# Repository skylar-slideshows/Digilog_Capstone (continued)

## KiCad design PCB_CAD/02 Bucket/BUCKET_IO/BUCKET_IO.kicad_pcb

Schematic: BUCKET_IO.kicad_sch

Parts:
J1: INPUTS; PinHeader_1x08_P2.54mm_Vertical
J2: INSERT; PinHeader_1x08_P2.54mm_Vertical
J3: IN; Jack_XLR-6.35mm_Neutrik_NCJ6FI-V-0_Vertical
J4: INSERT_OUT; Jack_6.35mm_Neutrik_NJ5FD-V_Vertical
J5: INSERT_RTN; Jack_6.35mm_Neutrik_NJ5FD-V_Vertical
J6: HI-Z; Jack_6.35mm_Neutrik_NJ5FD-V_Vertical

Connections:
/HIZ_IN: J1.7, J6.T
/INS_RTN+: J2.5, J5.T
/INS_RTN-: J2.7, J5.R
/INS_SEND+: J2.1, J4.T
/INS_SEND-: J2.3, J4.R
/LINE_COLD: J1.5, J3.R
/LINE_HOT: J1.4, J3.T
/MIC_COLD: J1.2, J3.3
/MIC_HOT: J1.1, J3.2
GND: J1.3, J1.6, J1.8, J2.2, J2.4, J2.6, J2.8, J3.1, J3.G, J3.S, J4.S, J5.S, J6.R, J6.S

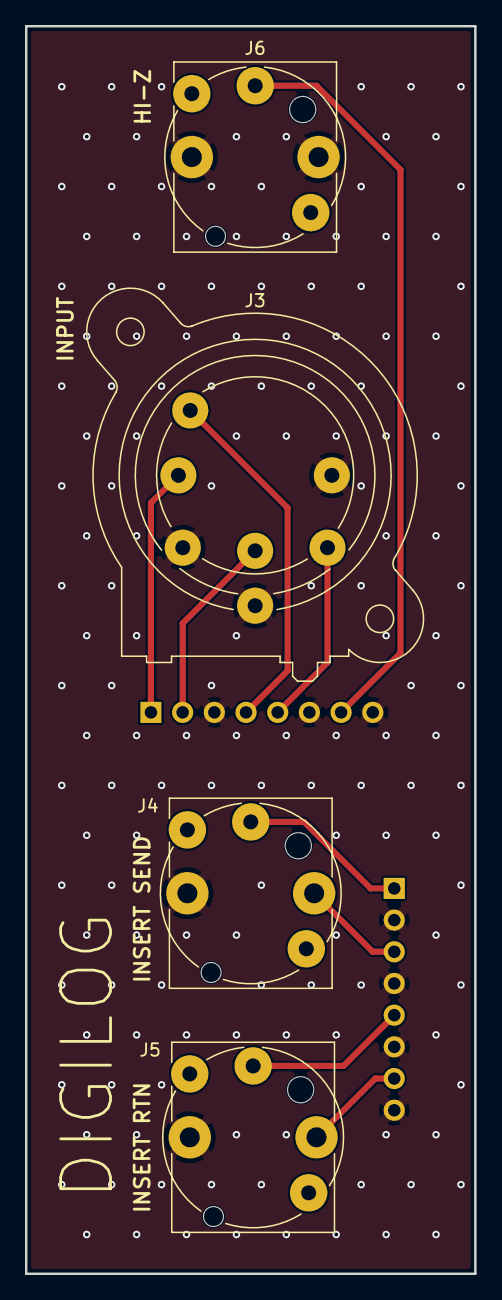
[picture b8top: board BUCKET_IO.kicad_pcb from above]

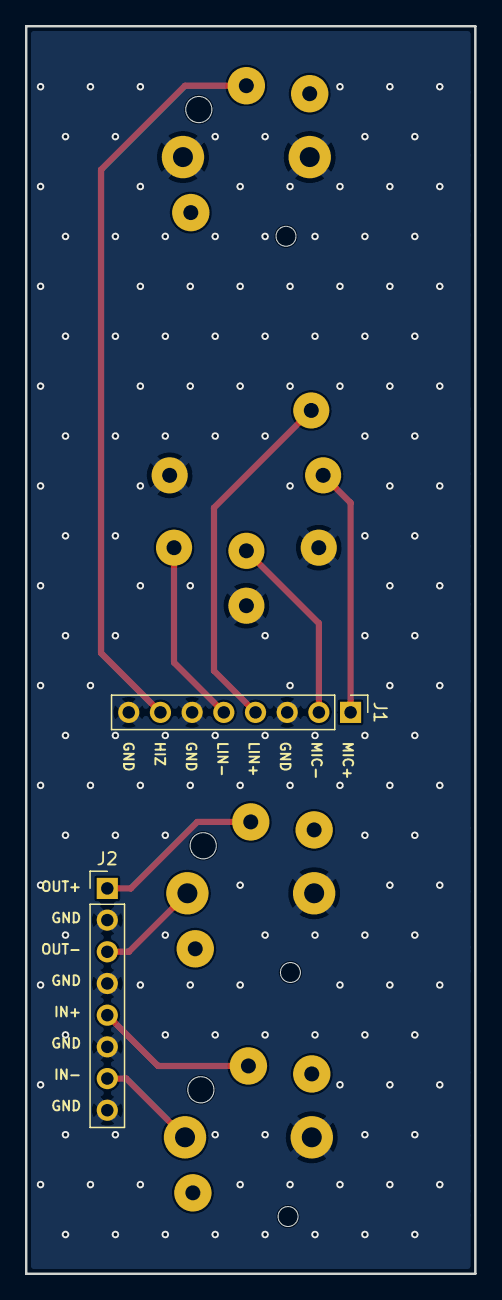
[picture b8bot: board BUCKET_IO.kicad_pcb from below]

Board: 2 copper layers, 36.0 x 100.0 mm, 6 parts (2 on the bottom side), 10 nets.

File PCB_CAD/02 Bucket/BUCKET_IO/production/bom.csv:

Designator,Footprint,Quantity,Value,LCSC Part #
J1,PinHeader_1x08_P2.54mm_Vertical,1,INPUTS,
J2,PinHeader_1x08_P2.54mm_Vertical,1,INSERT,
J3,Jack_XLR-6.35mm_Neutrik_NCJ6FI-V-0_Vertical,1,IN,
J4,Jack_6.35mm_Neutrik_NJ5FD-V_Vertical,1,INSERT_OUT,
J5,Jack_6.35mm_Neutrik_NJ5FD-V_Vertical,1,INSERT_RTN,

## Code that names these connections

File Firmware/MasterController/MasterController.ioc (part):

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Mcu.Name=STM32G474V(B-C-E)Tx
Mcu.Package=LQFP100
Mcu.UserName=STM32G474VETx
PA0.GPIOParameters=GPIO_Label
PA0.GPIO_Label=SCRUB_A
PA0.Signal=S_TIM2_CH1
PA1.GPIOParameters=GPIO_Label
PA1.GPIO_Label=SCRUB_B
PA1.Signal=S_TIM2_CH2
PA10.GPIOParameters=GPIO_Label
PA10.GPIO_Label=LDAC
PA10.Signal=GPIO_Output
PA11.Mode=Device
PA11.Signal=USB_DM
PA12.Mode=Device
PA12.Signal=USB_DP
PA13.GPIOParameters=GPIO_Label
PA13.GPIO_Label=SWD_SWDIO
PA13.Mode=Serial_Wire
PA13.Signal=SYS_JTMS-SWDIO
PA14.GPIOParameters=GPIO_Label
PA14.GPIO_Label=SWD_SWCLK
PA14.Mode=Serial_Wire
PA14.Signal=SYS_JTCK-SWCLK
PA15.GPIOParameters=PinState,GPIO_Label
PA15.GPIO_Label=DISK_CS
PA15.PinState=GPIO_PIN_SET
PA15.Signal=GPIO_Output
PA2.Mode=Asynchronous
PA2.Signal=USART2_TX
PA3.Mode=Asynchronous
PA3.Signal=USART2_RX
PA5.GPIOParameters=GPIO_Label
PA5.GPIO_Label=__MASTER_Clock
PA5.Mode=Full_Duplex_Master
PA5.Signal=SPI1_SCK
PA6.GPIOParameters=GPIO_Label
PA6.GPIO_Label=__MASTER_MISO
PA6.Mode=Full_Duplex_Master
PA6.Signal=SPI1_MISO
PA7.GPIOParameters=GPIO_Label
PA7.GPIO_Label=__MASTER_MOSI
PA7.Mode=Full_Duplex_Master
PA7.Signal=SPI1_MOSI
PA8.Mode=I2C
PA8.Signal=I2C2_SDA
PA9.GPIOParameters=GPIO_Label
PA9.GPIO_Label=I2C2_Clock
PA9.Mode=I2C
PA9.Signal=I2C2_SCL
PB10.GPIOParameters=GPIO_Label
PB10.GPIO_Label=DISP_INT
PB10.Signal=GPXTI10
PB13.GPIOParameters=GPIO_Label
PB13.GPIO_Label=LED_CLK
PB13.Mode=TX_Only_Simplex_Unidirect_Master
PB13.Signal=SPI2_SCK
PB14.GPIOParameters=GPIO_Label
PB14.GPIO_Label=LED_LAT
PB14.Signal=GPIO_Output
PB15.GPIOParameters=GPIO_Label
PB15.GPIO_Label=LED_DATA
PB15.Mode=TX_Only_Simplex_Unidirect_Master
PB15.Signal=SPI2_MOSI
PB3.GPIOParameters=PinState,GPIO_Label
PB3.GPIO_Label=CS_Bucket7
PB3.PinState=GPIO_PIN_SET
PB3.Signal=GPIO_Output
PB4.GPIOParameters=PinState,GPIO_Label
PB4.GPIO_Label=CS_Bucket6
PB4.PinState=GPIO_PIN_SET
PB4.Signal=GPIO_Output
PB5.GPIOParameters=PinState,GPIO_Label
PB5.GPIO_Label=CS_Bucket5
PB5.PinState=GPIO_PIN_SET
PB5.Signal=GPIO_Output
PB6.GPIOParameters=PinState,GPIO_Label
PB6.GPIO_Label=CS_Bucket4
PB6.PinState=GPIO_PIN_SET
PB6.Signal=GPIO_Output
PB7.GPIOParameters=PinState,GPIO_Label
PB7.GPIO_Label=CS_Bucket3
PB7.PinState=GPIO_PIN_SET
PB7.Signal=GPIO_Output
PB9.GPIOParameters=PinState,GPIO_Label
PB9.GPIO_Label=CS_Bucket2
PB9.PinState=GPIO_PIN_SET
PB9.Signal=GPIO_Output
PC1.GPIOParameters=GPIO_Label
PC1.GPIO_Label=LED_PWM
PC1.Signal=S_TIM1_CH2
PC10.GPIOParameters=GPIO_Label
PC10.GPIO_Label=DISK_SCK
PC10.Mode=Full_Duplex_Master
PC10.Signal=SPI3_SCK
PC11.GPIOParameters=GPIO_Label
PC11.GPIO_Label=DISK_MISO
PC11.Mode=Full_Duplex_Master
PC11.Signal=SPI3_MISO
PC12.GPIOParameters=GPIO_Label
PC12.GPIO_Label=DISK_MOSI
PC12.Mode=Full_Duplex_Master
PC12.Signal=SPI3_MOSI
PC2.GPIOParameters=GPIO_Label
PC2.GPIO_Label=Disp_PWM
PC2.Signal=S_TIM1_CH3
PD0.Mode=16b-d1
PD0.Signal=FMC_D2
PD1.Mode=16b-d1
PD1.Signal=FMC_D3
PD10.Mode=16b-d1
PD10.Signal=FMC_D15
PD14.Mode=16b-d1
PD14.Signal=FMC_D0
PD15.Mode=16b-d1
PD15.Signal=FMC_D1
PD3.GPIOParameters=GPIO_PuPd,GPIO_Label,GPIO_ModeDefaultOutputPP
PD3.GPIO_Label=DISP_RESET
PD3.GPIO_ModeDefaultOutputPP=GPIO_MODE_OUTPUT_OD
PD3.GPIO_PuPd=GPIO_NOPULL
PD3.Signal=GPIO_Output
PD4.Mode=Lcd1
PD4.Signal=FMC_NOE
PD5.Mode=Lcd1
PD5.Signal=FMC_NWE
PD6.Signal=FMC_NWAIT
PD7.Mode=NorPsramChipSelect1_1
PD7.Signal=FMC_NE1
PD8.Mode=16b-d1
PD8.Signal=FMC_D13
PD9.Mode=16b-d1
PD9.Signal=FMC_D14
PE0.GPIOParameters=PinState,GPIO_Label
PE0.GPIO_Label=CS_Bucket1
PE0.PinState=GPIO_PIN_SET
PE0.Signal=GPIO_Output
PE1.GPIOParameters=PinState,GPIO_Label
PE1.GPIO_Label=CS_Bucket0
PE1.PinState=GPIO_PIN_SET
PE1.Signal=GPIO_Output
PE10.Mode=16b-d1
PE10.Signal=FMC_D7
PE11.Mode=16b-d1
PE11.Signal=FMC_D8
PE12.Mode=16b-d1
PE12.Signal=FMC_D9
PE13.Mode=16b-d1
PE13.Signal=FMC_D10
PE14.Mode=16b-d1
PE14.Signal=FMC_D11
PE15.Mode=16b-d1
PE15.Signal=FMC_D12
PE2.GPIOParameters=GPIO_Label
PE2.GPIO_Label=LCV_AUX1
PE2.Signal=GPIO_Output
PE3.GPIOParameters=GPIO_Label
PE3.GPIO_Label=LCV_AUX2
PE3.Signal=GPIO_Output
PE4.GPIOParameters=GPIO_Label
PE4.GPIO_Label=LCV_AUX3
PE4.Signal=GPIO_Output
PE5.GPIOParameters=GPIO_Label
PE5.GPIO_Label=LCV_AUX4
PE5.Signal=GPIO_Output
PE7.Mode=16b-d1
PE7.Signal=FMC_D4
PE8.Mode=16b-d1
PE8.Signal=FMC_D5
PE9.Mode=16b-d1
PE9.Signal=FMC_D6
PF0-OSC_IN.GPIOParameters=GPIO_Label
PF0-OSC_IN.GPIO_Label=_OSC_IN
PF0-OSC_IN.Mode=HSE-External-Oscillator
PF0-OSC_IN.Signal=RCC_OSC_IN
PF1-OSC_OUT.GPIOParameters=GPIO_Label
PF1-OSC_OUT.GPIO_Label=_OSC_OUT
PF1-OSC_OUT.Mode=HSE-External-Oscillator
PF1-OSC_OUT.Signal=RCC_OSC_OUT
PF10.Mode=A0_1
PF10.Signal=FMC_A0
PF2.GPIOParameters=GPIO_Label
PF2.GPIO_Label=LED_TEST
PF2.Signal=GPIO_Output
RCC.HSE_VALUE=24000000
RCC.SYSCLKFreq_VALUE=170000000
RCC.SYSCLKSource=RCC_SYSCLKSOURCE_PLLCLK
board=custom

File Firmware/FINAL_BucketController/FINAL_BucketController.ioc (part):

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Mcu.Name=STM32G474V(B-C-E)Tx
Mcu.Package=LQFP100
Mcu.UserName=STM32G474VETx
PA0.GPIOParameters=GPIO_Label
PA0.GPIO_Label=SHIFTREG_Latch
PA0.Signal=GPIO_Output
PA1.GPIOParameters=GPIO_Label
PA1.GPIO_Label=F0_MoB
PA1.Signal=S_TIM2_CH2
PA10.GPIOParameters=GPIO_Label
PA10.GPIO_Label=F1_MoB
PA10.Signal=S_TIM2_CH4
PA11.GPIOParameters=GPIO_Label
PA11.GPIO_Label=SHIFTREG_Clock
PA11.Signal=GPIO_Output
PA12.GPIOParameters=GPIO_Label
PA12.GPIO_Label=SHIFTREG_Data
PA12.Signal=GPIO_Output
PA13.GPIOParameters=GPIO_Label
PA13.GPIO_Label=__SWDIO
PA13.Mode=Serial_Wire
PA13.Signal=SYS_JTMS-SWDIO
PA14.GPIOParameters=GPIO_Label
PA14.GPIO_Label=__SWCLK
PA14.Mode=Serial_Wire
PA14.Signal=SYS_JTCK-SWCLK
PA15.GPIOParameters=GPIO_Label
PA15.GPIO_Label=I2C1_Clock
PA15.Mode=I2C
PA15.Signal=I2C1_SCL
PA2.GPIOParameters=GPIO_Label
PA2.GPIO_Label=__USART2_TX
PA2.Mode=Asynchronous
PA2.Signal=USART2_TX
PA3.GPIOParameters=GPIO_Label
PA3.GPIO_Label=__USART2_RX
PA3.Mode=Asynchronous
PA3.Signal=USART2_RX
PA4.GPIOParameters=GPIO_Label
PA4.GPIO_Label=F2_MoB
PA4.Signal=S_TIM3_CH2
PA5.GPIOParameters=GPIO_Label
PA5.GPIO_Label=F0_MoA
PA5.Signal=S_TIM2_CH1
PA6.GPIOParameters=GPIO_Label
PA6.GPIO_Label=F2_MoA
PA6.Signal=S_TIM3_CH1
PA7.GPIOParameters=GPIO_Label
PA7.GPIO_Label=MASTER_MOSI
PA7.Mode=Full_Duplex_Slave
PA7.Signal=SPI1_MOSI
PA8.GPIOParameters=GPIO_Label
PA8.GPIO_Label=I2C2_Data
PA8.Mode=I2C
PA8.Signal=I2C2_SDA
PA9.GPIOParameters=GPIO_Label
PA9.GPIO_Label=I2C2_Clock
PA9.Mode=I2C
PA9.Signal=I2C2_SCL
PB0.GPIOParameters=GPIO_Label
PB0.GPIO_Label=F3_MoA
PB0.Signal=S_TIM3_CH3
PB1.GPIOParameters=GPIO_Label
PB1.GPIO_Label=COMP_ADC1
PB1.Mode=IN12-Single-Ended
PB1.Signal=ADC1_IN12
PB10.GPIOParameters=GPIO_Label
PB10.GPIO_Label=F1_MoA
PB10.Signal=S_TIM2_CH3
PB11.GPIOParameters=GPIO_Label
PB11.GPIO_Label=LED_Data
PB11.Signal=GPIO_Output
PB12.GPIOParameters=GPIO_Label
PB12.GPIO_Label=LED_Clock
PB12.Signal=GPIO_Output
PB13.GPIOParameters=GPIO_Label
PB13.GPIO_Label=COMP_CV1
PB13.Mode=Follower_Internally_Connected
PB13.Signal=OPAMP3_VINP
PB14.GPIOParameters=GPIO_Label
PB14.GPIO_Label=LED_Latch
PB14.Signal=GPIO_Output
PB15.GPIOParameters=GPIO_Label
PB15.GPIO_Label=DISP_CS3
PB15.Signal=GPIO_Output
PB2.GPIOParameters=GPIO_Label
PB2.GPIO_Label=DISP_CS0
PB2.Signal=GPIO_Output
PB3.GPIOParameters=GPIO_Label
PB3.GPIO_Label=MASTER_Clock
PB3.Mode=Full_Duplex_Slave
PB3.Signal=SPI1_SCK
PB4.GPIOParameters=GPIO_Label
PB4.GPIO_Label=MASTER_MISO
PB4.Mode=Full_Duplex_Slave
PB4.Signal=SPI1_MISO
PB5.GPIOParameters=GPIO_Label
PB5.GPIO_Label=I2C3_Data
PB5.Mode=I2C
PB5.Signal=I2C3_SDA
PB6.GPIOParameters=GPIO_Label
PB6.GPIO_Label=DAC_LDAC2
PB6.Signal=GPIO_Output
PB9.GPIOParameters=GPIO_Label
PB9.GPIO_Label=I2C1_Data
PB9.Mode=I2C
PB9.Signal=I2C1_SDA
PC0.GPIOParameters=GPIO_Label
PC0.GPIO_Label=MASTER_CS_IN
PC0.Signal=GPIO_Input
PC1.GPIOParameters=GPIO_Label
PC1.GPIO_Label=LED_PWM
PC1.Signal=S_TIM1_CH2
PC10.GPIOParameters=GPIO_Label
PC10.GPIO_Label=F3_Touch
PC10.Signal=GPIO_Input
PC11.GPIOParameters=GPIO_Label
PC11.GPIO_Label=F2_Touch
PC11.Signal=GPIO_Input
PC12.GPIOParameters=GPIO_Label
PC12.GPIO_Label=F1_Touch
PC12.Signal=GPIO_Input
PC2.GPIOParameters=GPIO_Label
PC2.GPIO_Label=DISP_PWM
PC2.Signal=S_TIM1_CH3
PC3.GPIOParameters=GPIO_Label
PC3.GPIO_Label=COMP_ADC0
PC3.Mode=IN9-Single-Ended
PC3.Signal=ADC1_IN9
PC4.GPIOParameters=GPIO_Label
PC4.GPIO_Label=COMP_ADC2
PC4.Mode=IN5-Single-Ended
PC4.Signal=ADC2_IN5
PC5.GPIOParameters=GPIO_Label
PC5.GPIO_Label=COMP_ADC3
PC5.Mode=IN11-Single-Ended
PC5.Signal=ADC2_IN11
PC6.GPIOParameters=GPIO_Label
PC6.GPIO_Label=I2C4_Clock
PC6.Mode=I2C
PC6.Signal=I2C4_SCL
PC7.GPIOParameters=GPIO_Label
PC7.GPIO_Label=I2C4_Data
PC7.Mode=I2C
PC7.Signal=I2C4_SDA
PC8.GPIOParameters=GPIO_Label
PC8.GPIO_Label=I2C3_Clock
PC8.Mode=I2C
PC8.Signal=I2C3_SCL
PD0.GPIOParameters=GPIO_Label
PD0.GPIO_Label=DISP_D2_FMC
PD0.Mode=8b-d1
PD0.Signal=FMC_D2
PD1.GPIOParameters=GPIO_Label
PD1.GPIO_Label=DISP_D3_FMC
PD1.Mode=8b-d1
PD1.Signal=FMC_D3
PD10.GPIOParameters=GPIO_Label
PD10.GPIO_Label=F1_ADC
PD10.Mode=IN7-Single-Ended
PD10.Signal=ADC3_IN7
PD11.GPIOParameters=GPIO_Label
PD11.GPIO_Label=COMP_CV2
PD11.Mode=Follower_Internally_Connected
PD11.Signal=OPAMP4_VINP
PD12.GPIOParameters=GPIO_Label
PD12.GPIO_Label=COMP_CV3
PD12.Mode=Follower_Internally_Connected
PD12.Signal=OPAMP5_VINP
PD13.GPIOParameters=GPIO_Label
PD13.GPIO_Label=F2_ADC
PD13.Mode=IN10-Single-Ended
PD13.Signal=ADC3_IN10
PD14.GPIOParameters=GPIO_Label
PD14.GPIO_Label=DISP_D0_FMC
PD14.Mode=8b-d1
PD14.Signal=FMC_D0
PD15.GPIOParameters=GPIO_Label
PD15.GPIO_Label=DISP_D1_FMC
PD15.Mode=8b-d1
PD15.Signal=FMC_D1
PD2.GPIOParameters=GPIO_Label
PD2.GPIO_Label=F0_Touch
PD2.Signal=GPIO_Input
PD3.GPIOParameters=GPIO_Label
PD3.GPIO_Label=DAC_LDAC4
PD3.Signal=GPIO_Output
PD4.GPIOParameters=GPIO_Label
PD4.GPIO_Label=DISP_NOE_FMC
PD4.Mode=Lcd1
PD4.Signal=FMC_NOE
PD5.GPIOParameters=GPIO_Label
PD5.GPIO_Label=DISP_NWE_FMC
PD5.Mode=Lcd1
PD5.Signal=FMC_NWE
PD6.GPIOParameters=GPIO_Label
PD6.GPIO_Label=DAC_LDAC3
PD6.Signal=GPIO_Output
PD7.GPIOParameters=GPIO_Label
PD7.GPIO_Label=DISP_NE1_FMC
PD7.Mode=NorPsramChipSelect1_1
PD7.Signal=FMC_NE1
PD9.GPIOParameters=GPIO_Label
PD9.GPIO_Label=COMP_CV0
PD9.Mode=Follower_Internally_Connected
PD9.Signal=OPAMP6_VINP
PE0.GPIOParameters=GPIO_Label
PE0.GPIO_Label=DAC_LDAC1
PE0.Signal=GPIO_Output
PE1.GPIOParameters=GPIO_Label
PE1.GPIO_Label=DAC_LDAC0
PE1.Signal=GPIO_Output
PE10.GPIOParameters=GPIO_Label
PE10.GPIO_Label=DISP_D7_FMC
PE10.Mode=8b-d1
PE10.Signal=FMC_D7
PE11.GPIOParameters=GPIO_Label
PE11.GPIO_Label=F3_ADC
PE11.Mode=IN15-Single-Ended
PE11.Signal=ADC3_IN15
PE13.GPIOParameters=GPIO_Label
PE13.GPIO_Label=F0_ADC
PE13.Mode=IN3-Single-Ended
PE13.Signal=ADC3_IN3
PE14.GPIOParameters=GPIO_Label
PE14.GPIO_Label=DISP_CS1
PE14.Signal=GPIO_Output
PE15.GPIOParameters=GPIO_Label
PE15.GPIO_Label=DISP_CS2
PE15.Signal=GPIO_Output
PE4.GPIOParameters=GPIO_Label
PE4.GPIO_Label=DISP_RST
PE4.Signal=GPIO_Output
PE5.GPIOParameters=GPIO_Label
PE5.GPIO_Label=F3_MoB
PE5.Signal=S_TIM3_CH4
PE7.GPIOParameters=GPIO_Label
PE7.GPIO_Label=DISP_D4_FMC
PE7.Mode=8b-d1
PE7.Signal=FMC_D4
PE8.GPIOParameters=GPIO_Label
PE8.GPIO_Label=DISP_D5_FMC
PE8.Mode=8b-d1
PE8.Signal=FMC_D5
PE9.GPIOParameters=GPIO_Label
PE9.GPIO_Label=DISP_D6_FMC
PE9.Mode=8b-d1
PE9.Signal=FMC_D6
PF0-OSC_IN.GPIOParameters=GPIO_Label
PF0-OSC_IN.GPIO_Label=__OSC_IN
PF0-OSC_IN.Mode=HSE-External-Oscillator
PF0-OSC_IN.Signal=RCC_OSC_IN
PF1-OSC_OUT.GPIOParameters=GPIO_Label
PF1-OSC_OUT.GPIO_Label=__OSC_OUT
PF1-OSC_OUT.Mode=HSE-External-Oscillator
PF1-OSC_OUT.Signal=RCC_OSC_OUT
PF10.GPIOParameters=GPIO_Label
PF10.GPIO_Label=DISP_A0_FMC
PF10.Mode=A0_1
PF10.Signal=FMC_A0
PF2.GPIOParameters=GPIO_Label
PF2.GPIO_Label=LED_TEST
PF2.Signal=GPIO_Output
RCC.HSE_VALUE=24000000
RCC.SYSCLKFreq_VALUE=16000000
board=custom

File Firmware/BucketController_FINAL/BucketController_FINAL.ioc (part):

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Mcu.Name=STM32G474V(B-C-E)Tx
Mcu.Package=LQFP100
Mcu.UserName=STM32G474VETx
PA0.GPIOParameters=GPIO_Label
PA0.GPIO_Label=SHIFTREG_Latch
PA0.Signal=GPIO_Output
PA1.GPIOParameters=GPIO_Speed,GPIO_Label
PA1.GPIO_Label=F0_MB
PA1.GPIO_Speed=GPIO_SPEED_FREQ_HIGH
PA1.Signal=S_TIM2_CH2
PA10.GPIOParameters=GPIO_Label
PA10.GPIO_Label=DISP_PWM
PA10.Signal=S_TIM1_CH3
PA11.GPIOParameters=GPIO_Label
PA11.GPIO_Label=SHIFTREG_Clock
PA11.Signal=GPIO_Output
PA12.GPIOParameters=GPIO_Label
PA12.GPIO_Label=SHIFTREG_Data
PA12.Signal=GPIO_Output
PA13.GPIOParameters=GPIO_Label
PA13.GPIO_Label=__SWDIO
PA13.Mode=Serial_Wire
PA13.Signal=SYS_JTMS-SWDIO
PA14.GPIOParameters=GPIO_Label
PA14.GPIO_Label=__SWCLK
PA14.Mode=Serial_Wire
PA14.Signal=SYS_JTCK-SWCLK
PA15.GPIOParameters=GPIO_Label
PA15.GPIO_Label=I2C1_Clock
PA15.Mode=I2C
PA15.Signal=I2C1_SCL
PA2.GPIOParameters=GPIO_Label
PA2.GPIO_Label=__USART2_TX
PA2.Mode=Asynchronous
PA2.Signal=USART2_TX
PA3.GPIOParameters=GPIO_Label
PA3.GPIO_Label=__USART2_RX
PA3.Mode=Asynchronous
PA3.Signal=USART2_RX
PA4.GPIOParameters=GPIO_Label
PA4.GPIO_Label=COMP_CV3
PA4.Signal=COMP_DAC11_group
PA5.GPIOParameters=GPIO_Speed,GPIO_Label
PA5.GPIO_Label=F0_MA
PA5.GPIO_Speed=GPIO_SPEED_FREQ_HIGH
PA5.Signal=S_TIM2_CH1
PA6.GPIOParameters=GPIO_Speed,GPIO_Label
PA6.GPIO_Label=F2_MA
PA6.GPIO_Speed=GPIO_SPEED_FREQ_HIGH
PA6.Signal=S_TIM3_CH1
PA7.GPIOParameters=GPIO_Speed,GPIO_Label
PA7.GPIO_Label=F2_MB
PA7.GPIO_Speed=GPIO_SPEED_FREQ_HIGH
PA7.Signal=S_TIM3_CH2
PA8.GPIOParameters=GPIO_Label
PA8.GPIO_Label=I2C2_Data
PA8.Mode=I2C
PA8.Signal=I2C2_SDA
PA9.GPIOParameters=GPIO_Label
PA9.GPIO_Label=I2C2_Clock
PA9.Mode=I2C
PA9.Signal=I2C2_SCL
PB1.GPIOParameters=GPIO_Label
PB1.GPIO_Label=COMP_CV1
PB1.Mode=Follower-DAC_OUT2-INP
PB1.Signal=OPAMP3_VOUT
PB10.GPIOParameters=GPIO_Speed,GPIO_Label
PB10.GPIO_Label=F1_MA
PB10.GPIO_Speed=GPIO_SPEED_FREQ_HIGH
PB10.Signal=S_TIM2_CH3
PB11.GPIOParameters=GPIO_Label
PB11.GPIO_Label=COMP_CV0
PB11.Mode=Follower-DAC_OUT2-INP
PB11.Signal=OPAMP6_VOUT
PB12.GPIOParameters=GPIO_Label
PB12.GPIO_Label=COMP_CV2
PB12.Mode=Follower-DAC_OUT2-INP
PB12.Signal=OPAMP4_VOUT
PB13.GPIOParameters=GPIO_Speed,GPIO_Label
PB13.GPIO_Label=LED_Clock
PB13.GPIO_Speed=GPIO_SPEED_FREQ_LOW
PB13.Mode=TX_Only_Simplex_Unidirect_Master
PB13.Signal=SPI2_SCK
PB14.GPIOParameters=GPIO_Label
PB14.GPIO_Label=LED_Latch
PB14.Signal=GPIO_Output
PB15.GPIOParameters=GPIO_Speed,GPIO_Label
PB15.GPIO_Label=LED_Data
PB15.GPIO_Speed=GPIO_SPEED_FREQ_LOW
PB15.Mode=TX_Only_Simplex_Unidirect_Master
PB15.Signal=SPI2_MOSI
PB2.GPIOParameters=GPIO_Label
PB2.GPIO_Label=F2_Touch
PB2.Signal=GPIO_Input
PB3.GPIOParameters=GPIO_Label
PB3.GPIO_Label=SPI1_Clock
PB3.Mode=Full_Duplex_Slave
PB3.Signal=SPI1_SCK
PB4.GPIOParameters=GPIO_Label
PB4.GPIO_Label=SPI1_MISO
PB4.Mode=Full_Duplex_Slave
PB4.Signal=SPI1_MISO
PB5.GPIOParameters=GPIO_Label
PB5.GPIO_Label=SPI1_MOSI
PB5.Mode=Full_Duplex_Slave
PB5.Signal=SPI1_MOSI
PB6.GPIOParameters=GPIO_Label
PB6.GPIO_Label=SPI1_CS_IN
PB6.Signal=GPIO_Input
PB7.GPIOParameters=GPIO_Speed,GPIO_Label
PB7.GPIO_Label=F3_MB
PB7.GPIO_Speed=GPIO_SPEED_FREQ_HIGH
PB7.Signal=S_TIM3_CH4
PB9.GPIOParameters=GPIO_Label
PB9.GPIO_Label=I2C1_Data
PB9.Mode=I2C
PB9.Signal=I2C1_SDA
PC0.GPIOParameters=GPIO_Label
PC0.GPIO_Label=F1_ADC
PC0.Mode=IN6-Single-Ended
PC0.Signal=ADC2_IN6
PC1.GPIOParameters=GPIO_Label
PC1.GPIO_Label=LED_PWM
PC1.Signal=S_TIM1_CH2
PC10.GPIOParameters=GPIO_Label
PC10.GPIO_Label=LDAC4
PC10.Signal=GPIO_Output
PC11.GPIOParameters=GPIO_Label
PC11.GPIO_Label=LDAC3
PC11.Signal=GPIO_Output
PC12.GPIOParameters=GPIO_Label
PC12.GPIO_Label=LDAC2
PC12.Signal=GPIO_Output
PC13.GPIOParameters=GPIO_Label
PC13.GPIO_Label=DISP_RST
PC13.Signal=GPIO_Output
PC2.GPIOParameters=GPIO_Label
PC2.GPIO_Label=F2_ADC
PC2.Mode=IN8-Single-Ended
PC2.Signal=ADC2_IN8
PC3.GPIOParameters=GPIO_Label
PC3.GPIO_Label=F3_ADC
PC3.Mode=IN9-Single-Ended
PC3.Signal=ADC2_IN9
PC4.GPIOParameters=GPIO_Label
PC4.GPIO_Label=F0_ADC
PC4.Mode=IN5-Single-Ended
PC4.Signal=ADC2_IN5
PC5.GPIOParameters=GPIO_Label
PC5.GPIO_Label=F1_Touch
PC5.Signal=GPIO_Input
PC6.GPIOParameters=GPIO_Label
PC6.GPIO_Label=I2C4_Clock
PC6.Mode=I2C
PC6.Signal=I2C4_SCL
PC7.GPIOParameters=GPIO_Label
PC7.GPIO_Label=I2C4_Data
PC7.Mode=I2C
PC7.Signal=I2C4_SDA
PC8.GPIOParameters=GPIO_Label
PC8.GPIO_Label=I2C3_Clock
PC8.Mode=I2C
PC8.Signal=I2C3_SCL
PC9.GPIOParameters=GPIO_Label
PC9.GPIO_Label=I2C3_Data
PC9.Mode=I2C
PC9.Signal=I2C3_SDA
PD0.GPIOParameters=GPIO_Label
PD0.GPIO_Label=DISP_D2_FMC
PD0.Mode=8b-d1
PD0.Signal=FMC_D2
PD1.GPIOParameters=GPIO_Label
PD1.GPIO_Label=DISP_D3_FMC
PD1.Mode=8b-d1
PD1.Signal=FMC_D3
PD10.GPIOParameters=GPIO_Label
PD10.GPIO_Label=COMP_ADC0
PD10.Mode=IN7-Single-Ended
PD10.Signal=ADC4_IN7
PD11.GPIOParameters=GPIO_Label
PD11.GPIO_Label=COMP_ADC1
PD11.Mode=IN8-Single-Ended
PD11.Signal=ADC4_IN8
PD12.GPIOParameters=GPIO_Label
PD12.GPIO_Label=COMP_ADC2
PD12.Mode=IN9-Single-Ended
PD12.Signal=ADC4_IN9
PD13.GPIOParameters=GPIO_Label
PD13.GPIO_Label=COMP_ADC3
PD13.Mode=IN10-Single-Ended
PD13.Signal=ADC4_IN10
PD14.GPIOParameters=GPIO_Label
PD14.GPIO_Label=DISP_D0_FMC
PD14.Mode=8b-d1
PD14.Signal=FMC_D0
PD15.GPIOParameters=GPIO_Label
PD15.GPIO_Label=DISP_D1_FMC
PD15.Mode=8b-d1
PD15.Signal=FMC_D1
PD2.GPIOParameters=GPIO_Label
PD2.GPIO_Label=LDAC0
PD2.Signal=GPIO_Output
PD3.GPIOParameters=GPIO_Label
PD3.GPIO_Label=LDAC1
PD3.Signal=GPIO_Output
PD4.GPIOParameters=GPIO_Label
PD4.GPIO_Label=DISP_NOE_FMC
PD4.Mode=Lcd1
PD4.Signal=FMC_NOE
PD5.GPIOParameters=GPIO_Label
PD5.GPIO_Label=DISP_NWE_FMC
PD5.Mode=Lcd1
PD5.Signal=FMC_NWE
PD6.GPIOParameters=GPIO_Speed,GPIO_Label
PD6.GPIO_Label=F1_MB
PD6.GPIO_Speed=GPIO_SPEED_FREQ_HIGH
PD6.Signal=S_TIM2_CH4
PD7.GPIOParameters=GPIO_Label
PD7.GPIO_Label=DISP_NE1_FMC
PD7.Mode=NorPsramChipSelect1_1
PD7.Signal=FMC_NE1
PE10.GPIOParameters=GPIO_Label
PE10.GPIO_Label=DISP_D7_FMC
PE10.Mode=8b-d1
PE10.Signal=FMC_D7
PE11.GPIOParameters=GPIO_Label
PE11.GPIO_Label=DISP_CS3
PE11.Signal=GPIO_Output
PE12.GPIOParameters=GPIO_Label
PE12.GPIO_Label=DISP_CS2
PE12.Signal=GPIO_Output
PE13.GPIOParameters=GPIO_Label
PE13.GPIO_Label=DISP_CS1
PE13.Signal=GPIO_Output
PE14.GPIOParameters=GPIO_Label
PE14.GPIO_Label=DISP_CS0
PE14.Signal=GPIO_Output
PE15.GPIOParameters=GPIO_Label
PE15.GPIO_Label=F3_Touch
PE15.Signal=GPIO_Input
PE4.GPIOParameters=GPIO_Speed,GPIO_Label
PE4.GPIO_Label=F3_MA
PE4.GPIO_Speed=GPIO_SPEED_FREQ_HIGH
PE4.Signal=S_TIM3_CH3
PE5.GPIOParameters=GPIO_Label
PE5.GPIO_Label=F0_Touch
PE5.Signal=GPIO_Input
PE7.GPIOParameters=GPIO_Label
PE7.GPIO_Label=DISP_D4_FMC
PE7.Mode=8b-d1
PE7.Signal=FMC_D4
PE8.GPIOParameters=GPIO_Label
PE8.GPIO_Label=DISP_D5_FMC
PE8.Mode=8b-d1
PE8.Signal=FMC_D5
PE9.GPIOParameters=GPIO_Label
PE9.GPIO_Label=DISP_D6_FMC
PE9.Mode=8b-d1
PE9.Signal=FMC_D6
PF0-OSC_IN.GPIOParameters=GPIO_Label
PF0-OSC_IN.GPIO_Label=__OSC_IN
PF0-OSC_IN.Mode=HSE-External-Oscillator
PF0-OSC_IN.Signal=RCC_OSC_IN
PF1-OSC_OUT.GPIOParameters=GPIO_Label
PF1-OSC_OUT.GPIO_Label=__OSC_OUT
PF1-OSC_OUT.Mode=HSE-External-Oscillator
PF1-OSC_OUT.Signal=RCC_OSC_OUT
PF10.GPIOParameters=GPIO_Label
PF10.GPIO_Label=DISP_A0_FMC
PF10.Mode=A0_1
PF10.Signal=FMC_A0
PF2.GPIOParameters=GPIO_Label
PF2.GPIO_Label=LED_TEST
PF2.Signal=GPIO_Output
RCC.HSE_VALUE=24000000
RCC.SYSCLKFreq_VALUE=170000000
RCC.SYSCLKSource=RCC_SYSCLKSOURCE_PLLCLK
board=custom
